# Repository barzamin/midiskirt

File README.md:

# MIDIskirt

A ~~period-accurate~~ C64 MIDI interface.

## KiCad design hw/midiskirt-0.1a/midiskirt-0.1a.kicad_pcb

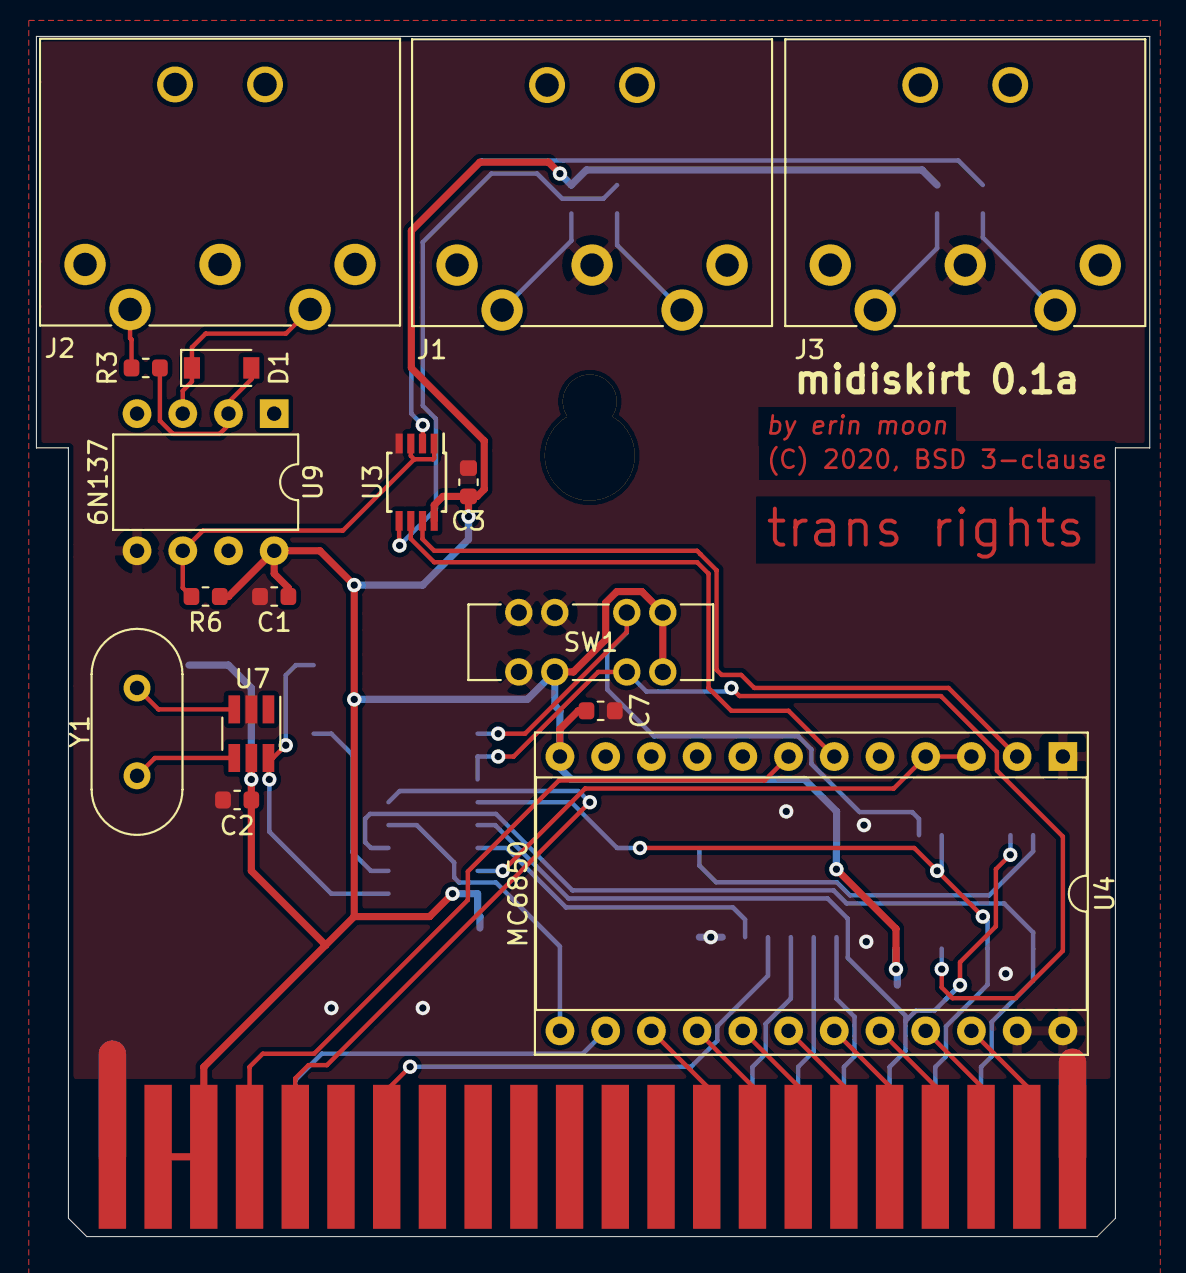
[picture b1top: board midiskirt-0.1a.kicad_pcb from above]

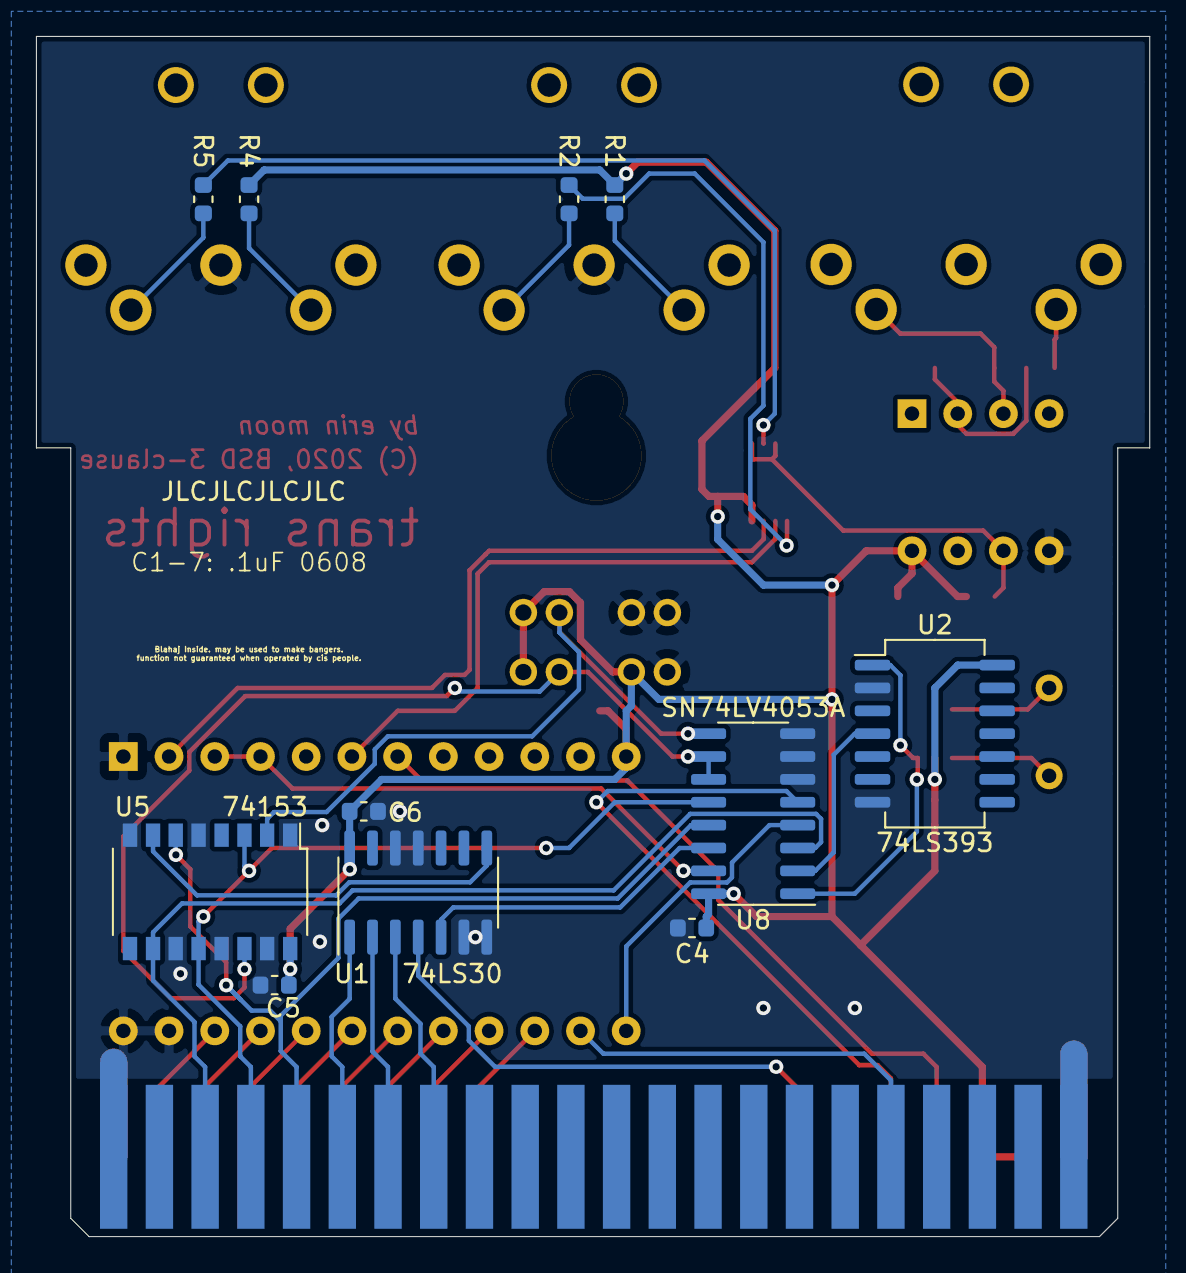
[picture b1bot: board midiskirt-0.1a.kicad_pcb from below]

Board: 2 copper layers, 61.8 x 66.7 mm, 28 parts (11 on the bottom side), 42 nets.

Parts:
C1, C2, C3, C4, C5, C6, C7: 0.1u; C_0603_1608Metric
D1: D; D_SOD-123
J1, J2, J3: DIN-5; SDS-50J
R1, R2, R3, R4, R5: 220; R_0603_1608Metric
R6: 10k; R_0603_1608Metric
SW1: SW_DP3T; C&K_JS203011CQN
U1: 74LS30; SOIC-14_3.9x8.7mm_P1.27mm
U2: 74LS393; SO-14_5.3x10.2mm_P1.27mm
U3: 74LVC3G16; TSSOP-8_3x3mm_P0.65mm
U4: MC6850; DIP-24_W15.24mm_Socket
U5: 74153; SOP-16_4.4x10.4mm_P1.27mm
U6: C64-Exp-Port; C64-Cart-NoSilkS
U7: SN74LVC1GX04; SOT-23-6_Handsoldering
U8: SN74LV4053A; SOIC-16_3.9x9.9mm_P1.27mm
U9: 6N137; DIP-8_W7.62mm
Y1: 2 MHz; Crystal_HC49-4H_Vertical

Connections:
+5V: C1.1, C2.1, C3.1, C4.1, C5.1, C6.1, C7.1, R1.1, R4.1, R6.1, SW1.2, SW1.4, SW1.8, U1.14, U2.14, U3.8, U4.12, U5.16, U6.2, U6.3, U7.5, U8.16, U9.8
/2mhz: U2.1, U7.6, U8.1
/500khz: U2.4, U8.2
/6850_CLK: U4.3, U4.4, U8.15
/RxD: U3.7, U4.2
/R~W~: U4.13, U8.4
/TxD: U3.6, U4.6
/a1: U5.10, U6.X, U8.3
/a2: U5.3, U5.12, U6.W, U8.12
/a3: U5.6, U6.V, U8.13
/a4: U1.1, U6.U
/a5: U1.2, U6.T
/a6: U1.3, U6.S
/cart-r~w~: U6.5, U8.5
/cs1: U1.8, U5.7
/d0: U4.22, U6.21
/d1: U4.21, U6.20
/d2: U4.20, U6.19
/d3: U4.19, U6.18
/d4: U4.18, U6.17
/d5: U4.17, U6.16
/d6: U4.16, U6.15
/d7: U4.15, U6.14
/midi_in: R6.2, U3.1, U3.3, U9.6
/midi_out: R5.1, U3.2
/midi_thru: R2.1, U3.5
/phi2: U4.14, U6.E
/sel_a: SW1.3, U5.14, U8.10, U8.11
/sel_b: SW1.7, U5.2, U8.9
/~io1~: U1.4, U6.7
/~irq~: U4.7, U6.4
GND: C1.2, C2.2, C3.2, C4.2, C5.2, C6.2, C7.2, J1.2, J3.2, SW1.1, SW1.5, SW1.6, U1.6, U1.7, U1.11, U1.12, U2.2, U2.7, U3.4, U4.1, U4.23, U4.24, U5.1, U5.5, U5.8, U5.11, U5.13, U5.15, U6.1, U6.22, U6.A, U6.Z, U7.2, U8.6, U8.7, U8.8, U9.5
unnamed: D1.1, J2.5, U9.3
unnamed: D1.2, R3.1, U9.2
unnamed: J1.4, R1.2
unnamed: J1.5, R2.2
unnamed: J2.4, R3.2
unnamed: J3.4, R4.2
unnamed: J3.5, R5.2
unnamed: U1.5, U8.14
unnamed: U7.3, Y1.1
unnamed: U7.4, Y1.2

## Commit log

2020-06-06 .gitignore
2020-06-06 kicad libs
2020-06-06 wip board
2020-06-06 cart: get rid of paste
2020-06-06 card: fix hole names
2020-06-07 probably bad, stuck version w discrete dip logic
2020-06-10 smt updates
2020-06-10 bump readme
2020-06-13 first design that seems orderable

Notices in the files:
hw/midiskirt-0.1a/midiskirt-0.1a.kicad_pcb:
(C) 2020, BSD 3-clause
